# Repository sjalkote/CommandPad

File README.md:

# CommandPad

This is supposed to be a keyboard macro pad that lets you set keys to custom keybinds, using mx switches, a rotary knob, and LEDs.

My attempt at a start-to-finish hardware project from scratch, including creating PCB designs, 3d print designs, and coding firmware.

### Bill of Parts

| Reference            | Qty | Value                | DNP | Exclude from BOM | Exclude from Board | Footprint                                                     | Datasheet                                                                  |
| -------------------- | --- | -------------------- | --- | ---------------- | ------------------ | ------------------------------------------------------------- | -------------------------------------------------------------------------- |
| D1,D2,D3,D4,D5,D6,D7 | 7   | Diode                |     |                  |                    | ScottoKeebs_Components:Diode_DO-35                            |                                                                            |
| DLED1,DLED2          | 2   | SK6812MINI           |     |                  |                    | LED_SMD:LED_SK6812MINI_PLCC4_3.5x3.5mm_P1.75mm                | https://cdn-shop.adafruit.com/product-files/2686/SK6812MINI_REV.01-1-2.pdf |
| J1                   | 1   | OLED_128x32          |     |                  |                    | 0.91 OLED Display:SSD1306-0.91-OLED-4pin-128x32               |                                                                            |
| S1,S2,S3,S4,S5,S6    | 6   | Keyswitch            |     |                  |                    | Button_Switch_Keyboard:SW_Cherry_MX_1.00u_PCB                 | ~                                                                          |
| SW1                  | 1   | RotaryEncoder_Switch |     |                  |                    | Rotary_Encoder:RotaryEncoder_Alps_EC11E-Switch_Vertical_H20mm | ~                                                                          |
| U1                   | 1   | XIAO-RP2040-DIP      |     |                  |                    | Seeed Studio XIAO Series Library:XIAO-RP2040-DIP              |                                                                            |

## Results

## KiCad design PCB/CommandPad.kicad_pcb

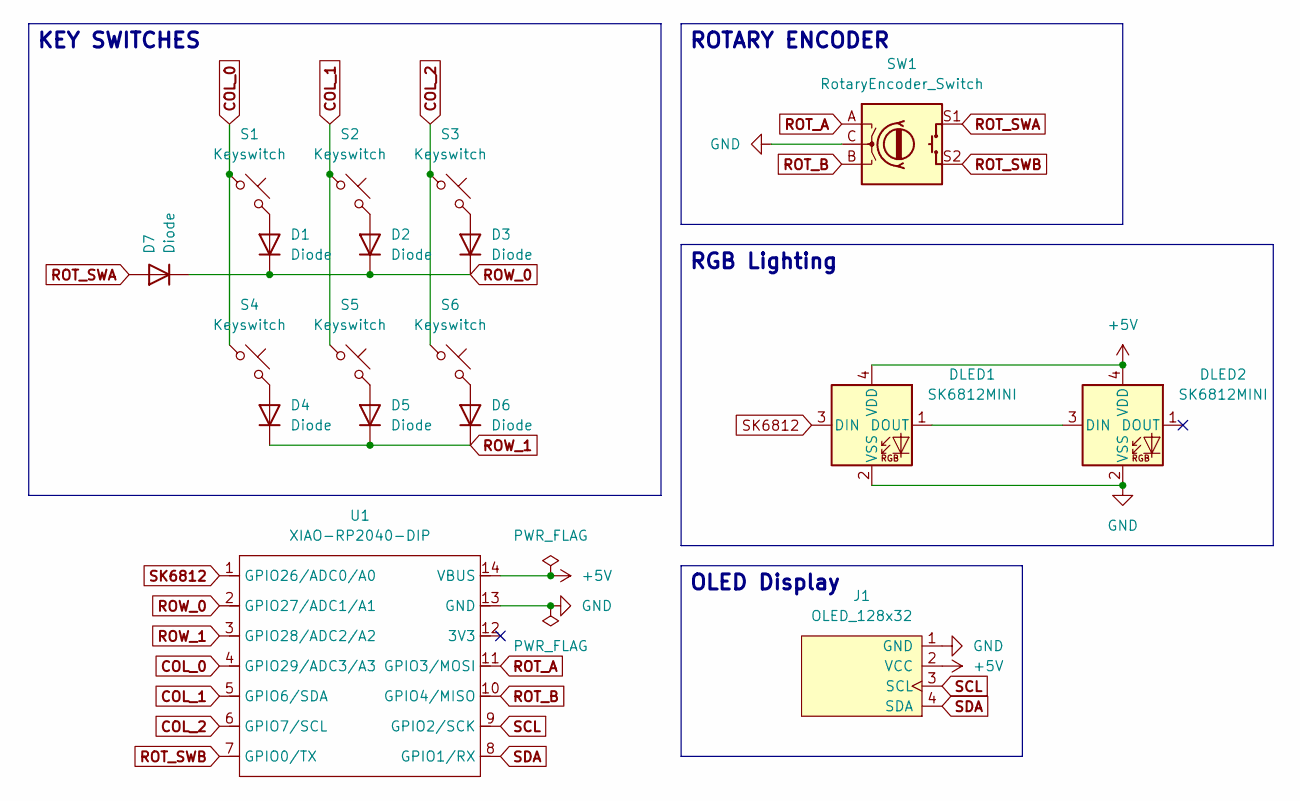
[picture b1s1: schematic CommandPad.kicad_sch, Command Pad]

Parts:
D1, D2, D3, D4, D5, D6, D7: Diode; Diode_DO-35
DLED1, DLED2: SK6812MINI; LED_SK6812MINI_PLCC4_3.5x3.5mm_P1.75mm
J1: OLED_128x32; SSD1306-0.91-OLED-4pin-128x32
S1, S2, S3, S4, S5, S6: Keyswitch; SW_Cherry_MX_1.00u_PCB
SW1: RotaryEncoder_Switch; RotaryEncoder_Alps_EC11E-Switch_Vertical_H20mm
U1: XIAO-RP2040-DIP

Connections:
+5V: DLED1.4 (VDD), DLED2.4 (VDD), J1.2 (VCC), U1.14 (VBUS)
COL_0: S1.1, S4.1, U1.4 (GPIO29/ADC3/A3)
COL_1: S2.1, S5.1, U1.5 (GPIO6/SDA)
COL_2: S3.1, S6.1, U1.6 (GPIO7/SCL)
GND: DLED1.2 (VSS), DLED2.2 (VSS), J1.1 (GND), SW1.C, U1.13 (GND)
unnamed: D1.2 (A), S1.2
unnamed: D2.2 (A), S2.2
unnamed: D3.2 (A), S3.2
unnamed: D4.2 (A), S4.2
unnamed: D5.2 (A), S5.2
unnamed: D6.2 (A), S6.2
unnamed: DLED1.1 (DOUT), DLED2.3 (DIN)
ROT_A: SW1.A, U1.11 (GPIO3/MOSI)
ROT_B: SW1.B, U1.10 (GPIO4/MISO)
ROT_SWA: D7.2 (A), SW1.S1
ROT_SWB: SW1.S2, U1.7 (GPIO0/TX)
ROW_0: D1.1 (K), D2.1 (K), D3.1 (K), D7.1 (K), U1.2 (GPIO27/ADC1/A1)
ROW_1: D4.1 (K), D5.1 (K), D6.1 (K), U1.3 (GPIO28/ADC2/A2)
SCL: J1.3 (SCL), U1.9 (GPIO2/SCK)
SDA: J1.4 (SDA), U1.8 (GPIO1/RX)
SK6812: DLED1.3 (DIN), U1.1 (GPIO26/ADC0/A0)

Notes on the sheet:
OLED Display
RGB Lighting
ROTARY ENCODER
KEY SWITCHES

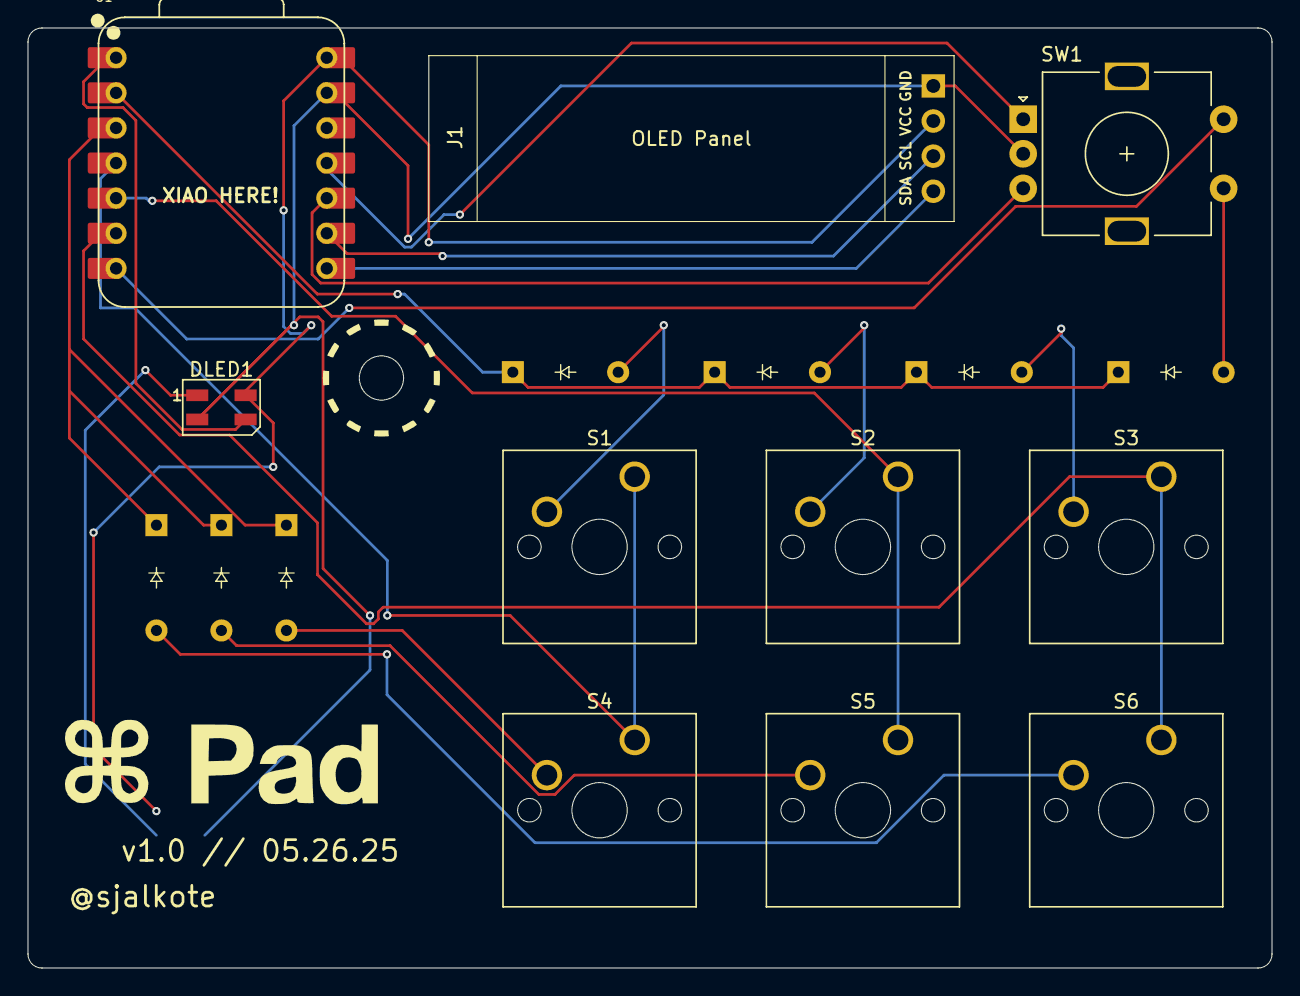
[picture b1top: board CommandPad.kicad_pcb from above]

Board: 2 copper layers, 90.0 x 68.0 mm, 20 parts (1 on the bottom side), 21 nets.

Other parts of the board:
M3: LOGO
M3x16mm: MountingHole_3.2mm_M3

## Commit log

2025-05-26 Complete schematic design with 0 electrical errors
2025-05-26 Add temporary `README.md`
2025-05-26 Finalized PCB design
2025-05-26 Finish project and restructured folders
2025-05-26 Added firmware
2025-05-26 updated pcb
2025-05-26 cleanup project
2025-05-26 Add production files
2025-05-26 Add BOP to `README.md`
2025-05-26 Add images
2025-05-26 Finished `README.md`
